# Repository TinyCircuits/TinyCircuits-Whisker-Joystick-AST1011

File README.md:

# TinyCircuits Wireling Joystick
# AST1011 Rev2

The design files are located under design_files/ for the TinyCircuits AST1011 Rev 2 PCB. This is a Wireling board which lets you use a discrete joystick for four directional inputs to your TinyDuino! This Up, Down, Left, Right joystick outputs data to an SX1502 I2C I/O expander. This data can then acquired by the main processor via I2C.
Format is in Cadsoft Eagle format - Eagle version 6.2 was used for the original design.

For more infomation on this, check out the product page at TinyCircuits.com

# License:

Design by TinyCircuits.
All design files are released under the Creative Commons Attribution Share-Alike 3.0 License, see the following link for details: http://creativecommons.org/licenses/by-sa/3.0

All text above must be included in any redistribution or derived design

This project uses designs and concepts developed as part of the Arduino project and the LilyPad project.  The TinyCircuits design files themselves (schematics, PCB and libraries) are not directly derived from these works' design files and have been created new, however the concepts and basic architecture behind the TinyDuino and TinyLily products are derived and we thank the hard work of the organizations below for their contributions to open-source hardware:
  
Original Arduino Uno Design by Team Arduino

LilyPad Arduino Design by Leah Buechley and Sparkfun Electronics

Please support the open-source hardware community

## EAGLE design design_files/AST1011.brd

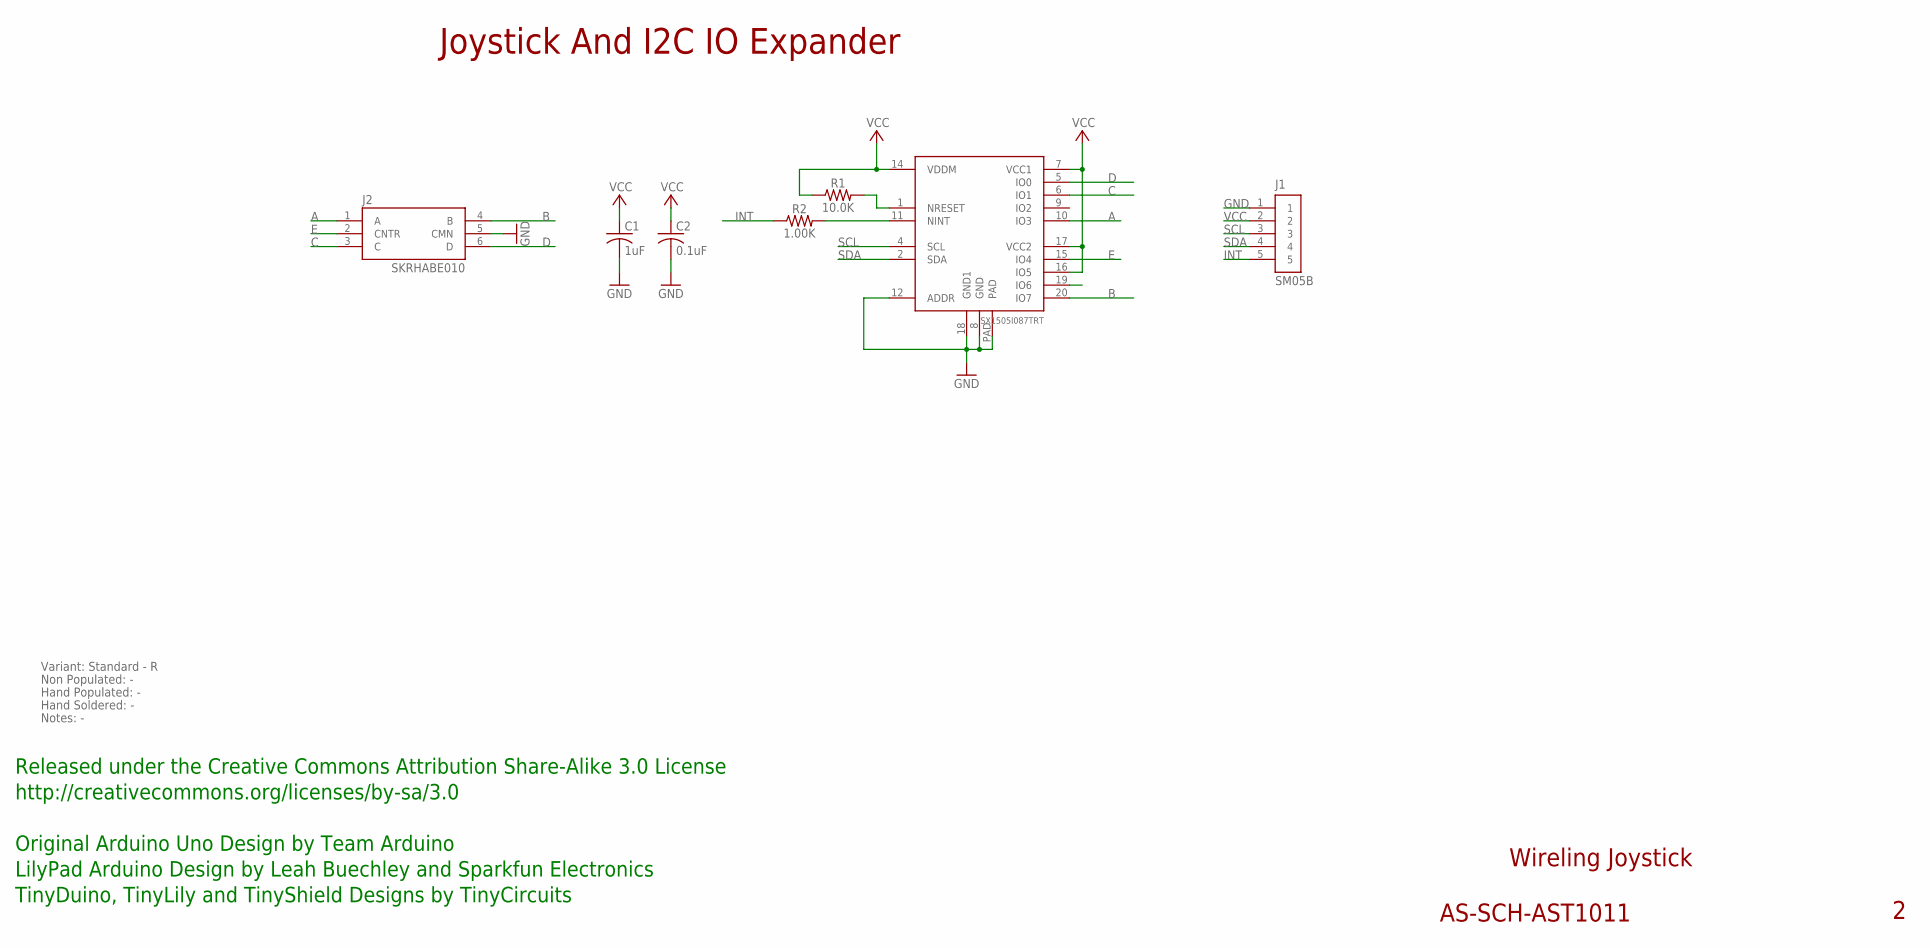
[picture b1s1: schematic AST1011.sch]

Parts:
C1: 1uF; C0402; PARTNO AS-ITM-00105
C2: 0.1uF; C0402
J1: SM05B; JST_SH_5X1_EDGE
J2: SKRHABE010; SKRHA_C
R1: 10.0K; 0402
R2: 1.00K; 0402
U1: SX1505I087TRT; QFN-UT20

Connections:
A: J2.1 (A), U1.10 (IO3)
B: J2.4 (B), U1.20 (IO7)
C: J2.3 (C), U1.6 (IO1)
D: J2.6 (D), U1.5 (IO0)
E: J2.2 (CNTR), U1.15 (IO4)
GND: C1.2, C2.2, J1.1, J2.5 (CMN), U1.8 (GND), U1.12 (ADDR), U1.18 (GND1), U1.PAD
INT: J1.5, R2.1
unnamed: R2.2, U1.11 (NINT)
unnamed: R1.2, U1.1 (NRESET)
SCL: J1.3, U1.4 (SCL)
SDA: J1.4, U1.2 (SDA)
VCC: C1.1, C2.1, J1.2, R1.1, U1.7 (VCC1), U1.14 (VDDM), U1.16 (IO5), U1.17 (VCC2)

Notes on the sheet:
Wireling Joystick
AS-SCH-AST1011
Joystick And I2C IO Expander
Released under the Creative Commons Attribution Share-Alike 3.0 License
http://creativecommons.org/licenses/by-sa/3.0
Original Arduino Uno Design by Team Arduino
TinyDuino, TinyLily and TinyShield Designs by TinyCircuits
LilyPad Arduino Design by Leah Buechley and Sparkfun Electronics
Non Populated: -
Hand Populated: -
Hand Soldered: -
Variant: Standard - R
Notes: -

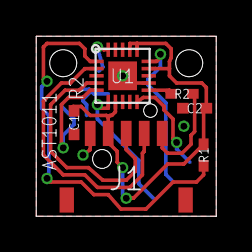
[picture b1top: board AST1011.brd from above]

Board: 2 copper layers, 10.0 x 10.0 mm, 8 parts (1 on the bottom side), 12 nets.

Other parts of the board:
U$1: DOCFIELD-TINYCIRCUITS-PCB

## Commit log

2019-07-17 added images
2019-07-18 changed code to use Port 0
2019-07-30 updated to use Port 0
2019-08-02 added datasheet
2019-10-24 fix program
2019-11-26 update program
2019-12-17 updated documentation
2020-01-02 updated library and example code
2020-01-02 updated sketch
2020-02-04 mass image update
2020-02-06 added libraries to example folder
2020-02-07 image update
2020-02-17 wrong datasheet
2020-02-17 remove
2020-02-18 Program updates
2020-02-18 kill library
2020-03-09 new program:
2020-08-28 Add CAD data
